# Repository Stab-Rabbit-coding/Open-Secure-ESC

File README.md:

# Open Source Trustworthy Electronic Speed Control

All builds:

MCU: **TI MSPM0G3518-Q1**, package RHB (VQFN-32, 5x5mm), orderable `M0G3518QRHBRQ1` [44] — pin map VERIFIED, standard package for all builds as of 2026-09-06 (`docs/solutions/architecture-patterns/bom-creepage-audit-can485-faraday.md` finding #1; supersedes the PM/LQFP-64 package, same die, ~4x smaller footprint). Supersedes the NXP S32K144 [31] as of 2026-08-10 (`TODO.md` §13.1; migration record in [`docs/HANDOFF-mcu-swap-s32k144-to-mspm0g3518.md`](docs/HANDOFF-mcu-swap-s32k144-to-mspm0g3518.md)), for its AES-128/256 accelerator with GCM/CMAC and hardware keystore, which lifted the AES-128 ceiling the S32K144's SHE-compliant CSEc imposed.

> **The two lines below still describe the S32K144 and its CSEc, which is no longer the MCU in any build.** They are left in place because the swap's *security* consequences are unfinished work, not a documentation lag — `docs/secure-element-architecture.md` has not yet been revisited (`TODO.md` §13.1.e), so rewriting the summary here would assert a conclusion nobody has reached. Treat every CSEc statement below as describing a superseded design until §13.1.e closes. The OPTIGA Trust M's role is unaffected: the MSPM0's AES engine is still symmetric, so the asymmetric layer is still required.

Message authentication: on-chip CSEc (Cryptographic Services Engine, SHE-compliant) security module built into the S32K144 [31] — no discrete TPM (the previously used Infineon SLB9672 [2] has been dropped from this design)
Root of trust: Infineon OPTIGA™ Trust M V3 secure element [45] over I²C (schematic `U2`) — device identity (ECDSA over a fab-provisioned key + X.509 certificate) and ephemeral session-key agreement (ECDHE). This is a secure element, **not** a TPM: it supplies the asymmetric layer CSEc structurally lacks, while CSEc keeps the per-frame AES-128 CMAC hot path. The split, and the 5 s security-monitor budget that forces it, are documented in [`docs/secure-element-architecture.md`](docs/secure-element-architecture.md)

Build Options:

* Motor speed sensor: ADC/DIO/SPI shaft sensor input (Hall / encoder / analog tach / magnetic absolute SSI-SPI, e.g. AEAT-8800-Q24 [64])
* Motor type: Brushed (Tier-1 integrated H-bridge DRV8874-Q1 [63]) / Brushless
* Holding brake: None (default) / Low-side solenoid driver, spring-applied (de-energised = engaged; TPL7407L [66]) — see `docs/decision-matrix.xlsx` "Holding Brake"
* Voltage: 2S, 4S, 6S, 8S, 12S
* Amperage: 10A, 20A, 30A, 40A, 50A, 80A, 120A
* Protocol: PWM, SBus, DBus, UART, TTL, SPI, RS-232 [3], RS-485 [4], CAN2.0 [5], CAN-FD [6], MIL-STD-1553B [7]
* Control: Open, Closed-Diff, Closed-PID
* EMI Hardening: None, Isolation, Grounding, Faraday
* Wire Egress: Opposite-end (default), Same-end opposite faces (both conductor groups leave one board end, phases on F.Cu and pack on B.Cu, shielded by the inner GND planes)
* Form Factor: Flat (default), Faceted rigid-flex (for mounting inside a curved host; strip width and sagitta derive from the host bore radius — see `docs/tools/strip_width.py`)
* Ingress & environmental protection: Splash/spray variants (target IPX4–IPX6, IEC 60529 [56]) air-cooled via an open aspirated path; Sealed/immersion variants (target IPX7–IPX8, up to NEMA 6P equivalent) shall use a metal conduction cooling path with no air exchange — these are two distinct mechanical designs, not one IP-rating dial (see `docs/design-waterproofing-and-thermal-management.md`).

## Repository layout

* `symbols/` — shared KiCad symbol library (one `.kicad_sym` per component),
  generated from citable pin specs; see `symbols/README.md`.
* `builds/<voltage>/<amperage>/<variant>/` — per-build instantiation of the
  axis options above: a descriptive `README.md` (BOM drawn from
  `docs/decision-matrix.xlsx`, with citations), a `kicad/` subfolder
  (schematic + shared-library wiring), and a `gerbers/` subfolder
  (fabrication output once a layout exists). Example:
  `builds/6s/50A/CAN_485_faraday/`.
* `docs/decision-matrix.xlsx` — per-axis BOM/workflow decision matrix that
  every build folder is generated from.
* `PROJECT_INDEX.md` — index of every active folder and file, with the
  conventions worth knowing before editing.

## License

Licensed under the CERN Open Hardware Licence Version 2 — Permissive
(CERN-OHL-P v2) [8]. See `LICENSE`.

## Governance

Contributions (human or AI) are governed by `AGENTS.md`. All citations
above are indexed in `REFERENCES.md`. Work is tracked in `TODO.md`.

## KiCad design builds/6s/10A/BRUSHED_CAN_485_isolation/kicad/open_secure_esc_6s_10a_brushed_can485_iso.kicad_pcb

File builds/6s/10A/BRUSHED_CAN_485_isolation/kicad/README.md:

# kicad/ — 6S / 10A / BRUSHED / CAN-FD+RS-485 / Isolation

Governed by `AGENTS.md`. Build spec: `../README.md`. Plan: Serenity-UAV
`docs/plans/2026-09-17-001-feat-tilt-controller-open-secure-esc-build-plan.md` (U4).

## Status

| Item | State (2026-09-17) |
| --- | --- |
| Schematic | Generated by `tools/gen_schematic.py`; **ERC 0 errors / 0 warnings** at `--severity-all` (kicad-cli 9.0.2, project context) |
| Netlist | 90 nets, 81 parts; every intended net present, no single-pin nets, PMODE → GND, IMODE strap, nFAULT pull-up, BRAKE_EN pull-down and VM-sense divider all confirmed from `kicad-cli sch export netlist` |
| PCB | Not started — no `.kicad_pcb`; see `../gerbers/README.md` for the gate list |
| Envelope check | `docs/tools/isolation_envelope.py --widest 7.0 --board-width 36.5` → minimum width 25.96 mm for the widest non-isolated part (a 7 mm inductor class) to sit between the two isolated rows; at 36.5 mm the check passes with 12.8 mm of margin, so control sits alongside comms with no creepage band in the stack |

## How the sheet is built (read before editing)

The schematic is **label-wired, not drawn**: every pin that carries a net has
a global label placed on its connection point and every unused pin has a
no-connect flag there. There are no wires. This is deliberate — it removes
the hand-wiring Y-sign trap (`docs/solutions/architecture-patterns/schematic-pin-y-sign-when-hand-wiring.md`)
and makes the netlist the proof of connectivity. The consequence is that the
sheet is a netlist you can open in KiCad, not a diagram arranged for
reading; a human-arranged view is a follow-up (`TODO.md` 18.6).

`tools/gen_schematic.py` is the single source. It reads pin geometry from the
same `symbols/*.kicad_sym` files it embeds, so a regenerated symbol cannot
drift from the sheet. `python3 tools/gen_schematic.py --check` exits 0 only
when the committed sheet equals the generator output — run it before every
commit that touches either. **Do not edit the `.kicad_sch` by hand**; if
KiCad's GUI is used to rearrange it, port the change into the generator
or the next regeneration will drop it (the 6S/50A build's divergence trap).

## Files

| File | What it is |
| --- | --- |
| `open_secure_esc_6s_10a_brushed_can485_iso.kicad_sch` | The schematic (KiCad 9 format 20250114), generated |
| `open_secure_esc_6s_10a_brushed_can485_iso.kicad_pro` | Project file: net classes Default / Power (1.5 mm) / Motor (1.5 mm) / Isolated / Sense with the net assignments below |
| `open_secure_esc_6s_10a_brushed_can485_iso.kicad_dru` | Custom rules: power/motor/sense conductor spacing, isolation-barrier no-via rule (7.5 mm, [9] Table 6) with its negative control |
| `sym-lib-table` | Symbol bindings to `symbols/`, each `descr` carrying the REFERENCES tag and verification note |
| `fp-lib-table` | `Open_Secure_ESC.pretty` (this repo's TI PWP0016J / DDA0008B / OPTIGA USON-10 footprints) |
| `tools/gen_schematic.py` | Generator (kiutils-free) |

## Net classes

| Class | Nets | Why |
| --- | --- | --- |
| Power | VBAT, GND, VMOT, 3V3, U6_SW, U8_SW | 3 A branch, 2.9 A motor stall; width sized in the layout follow-up (IPC-2152 [46] unread) |
| Motor | MOT_OUT1, MOT_OUT2, SOL_N | Bridge outputs and the solenoid sink |
| Isolated | CAN_H/L, CAN_VISOIN/OUT, CAN_ISO_GND, CAN_GNDISO, RS485_A/B, RS485_VISOIN/OUT, RS485_ISO_GND, RS485_GNDISO | Isolated side of both transceivers; the `.kicad_dru` via rule keys on this class |
| Sense | ADC_IPROPI, ADC_VM, ADC_VBUS, BRAKE_SENSE, U5_VREF, U5_IPROPI | Analog, 0.3 mm spacing |

## Libraries (sym-lib-table)

| Nickname | Symbol | Pin-map status |
| --- | --- | --- |
| `MSPM0G3518_Q1_RHB_TILT` | U1 MCU, tilt-build role names, all 32 pins | VERIFIED — [44] Fig. 6-6 / Table 6-2 (`symbols/specs/MSPM0G3518_Q1_RHB_TILT.json`) |
| `OPTIGA_TRUST_M` | U2 | VERIFIED — [45] p.17 Table 6 |
| `ADM3055E_ADM3057E` | U3 (ADM3057E) | VERIFIED — [10]; part Candidate |
| `ADM2582E_ADM2587E` | U4 (ADM2587E) | VERIFIED — [9]; part Candidate |
| `DRV8874_Q1` | U5 | VERIFIED — [63] §5, cross-checked [62] |
| `TPS54560B` | U6, U8 | VERIFIED — [65] §5 |
| `TPL7407L` | U7 | VERIFIED — [66] §5 |
| `BLM15HD182SN1D` | FB1–FB4 | VERIFIED — [53] |
| `AEAT_8800_Q24` | (not placed; off-board sensor daughter) | VERIFIED — [64] |
| `Open_Secure_ESC_Generic` | R, C, Conn_01x02/04, PWR_FLAG | Generic |
| `Device`, `Connector_Generic` (KiCad stock) | L1/L2, D1/D2, J7 | Generic; parts UNVERIFIED — see `../README.md` |

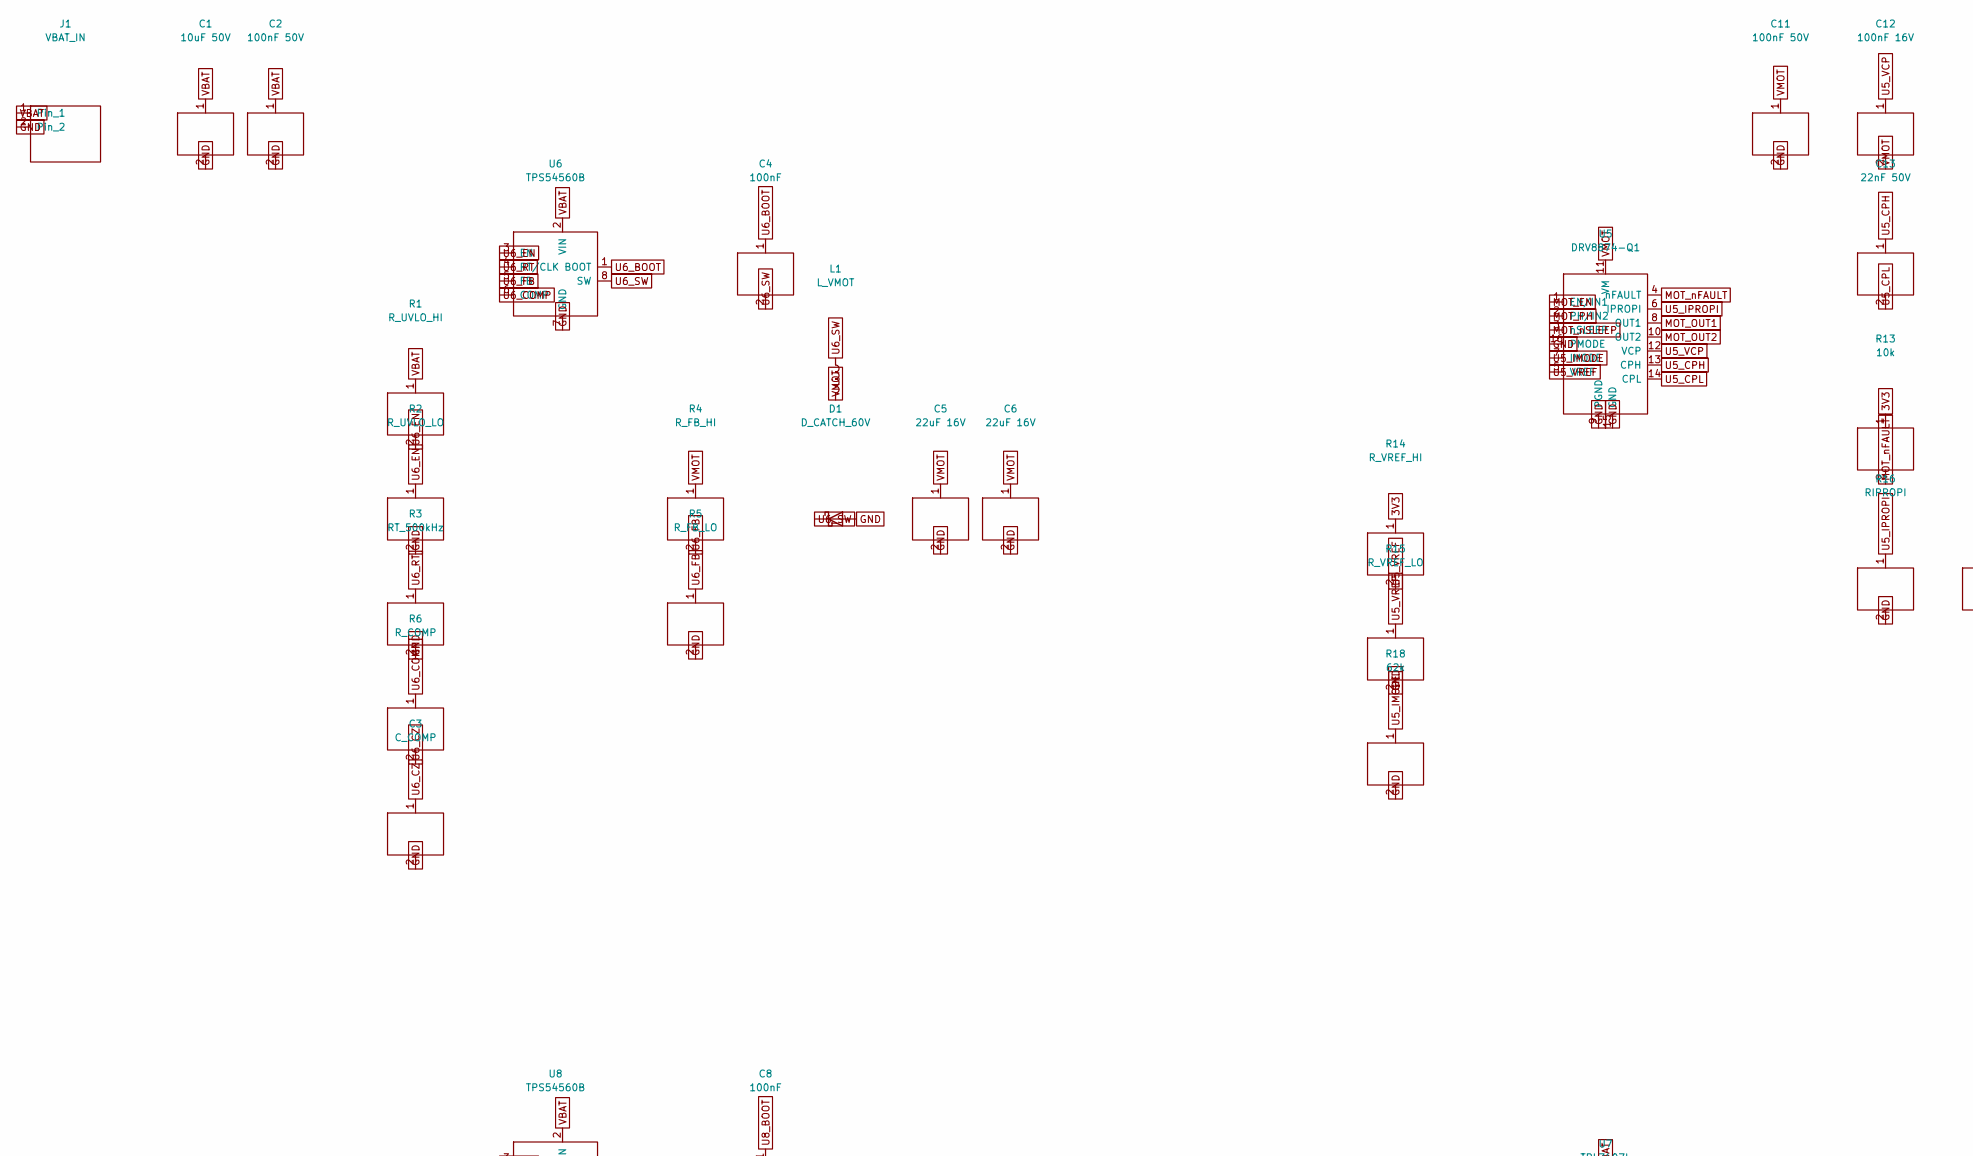
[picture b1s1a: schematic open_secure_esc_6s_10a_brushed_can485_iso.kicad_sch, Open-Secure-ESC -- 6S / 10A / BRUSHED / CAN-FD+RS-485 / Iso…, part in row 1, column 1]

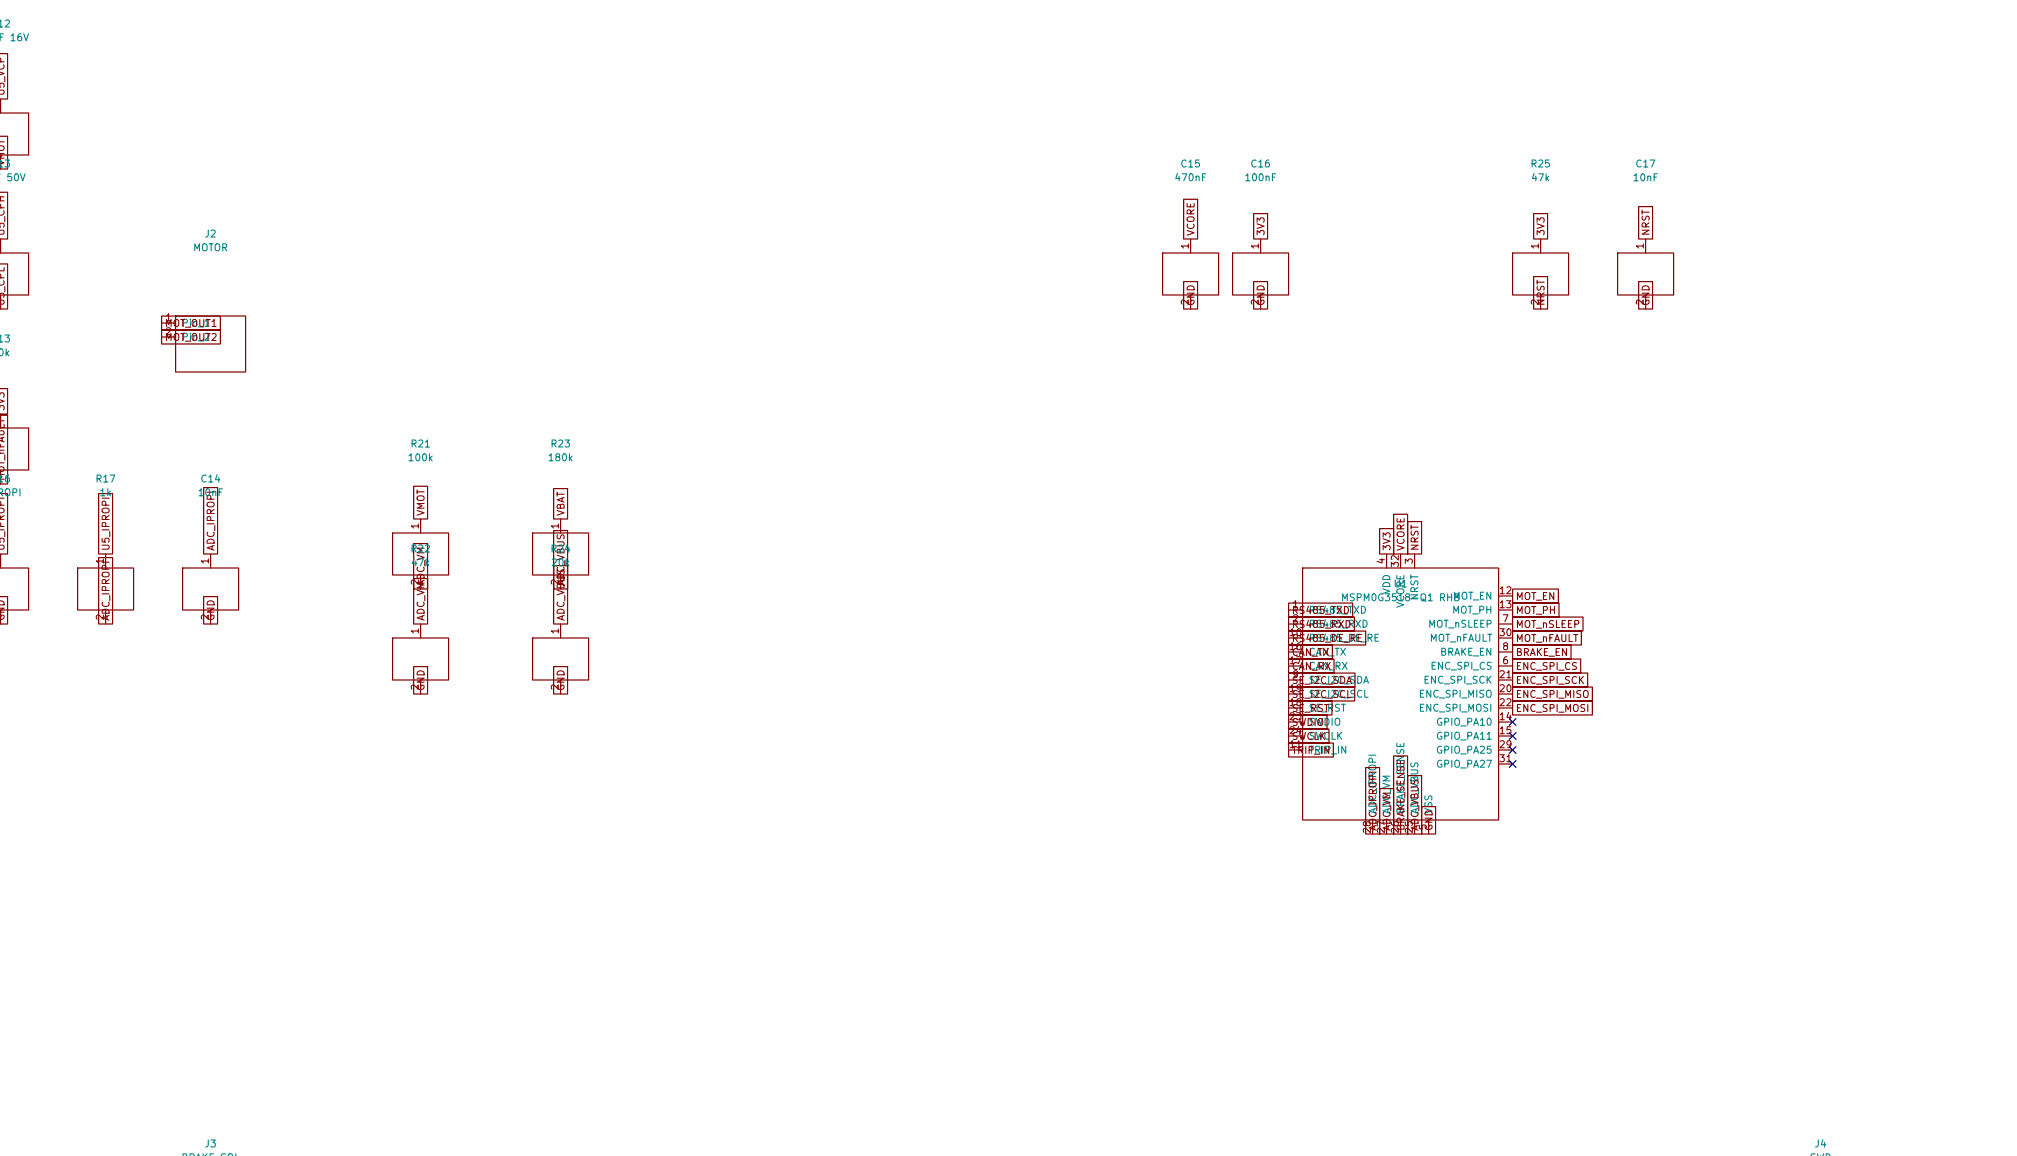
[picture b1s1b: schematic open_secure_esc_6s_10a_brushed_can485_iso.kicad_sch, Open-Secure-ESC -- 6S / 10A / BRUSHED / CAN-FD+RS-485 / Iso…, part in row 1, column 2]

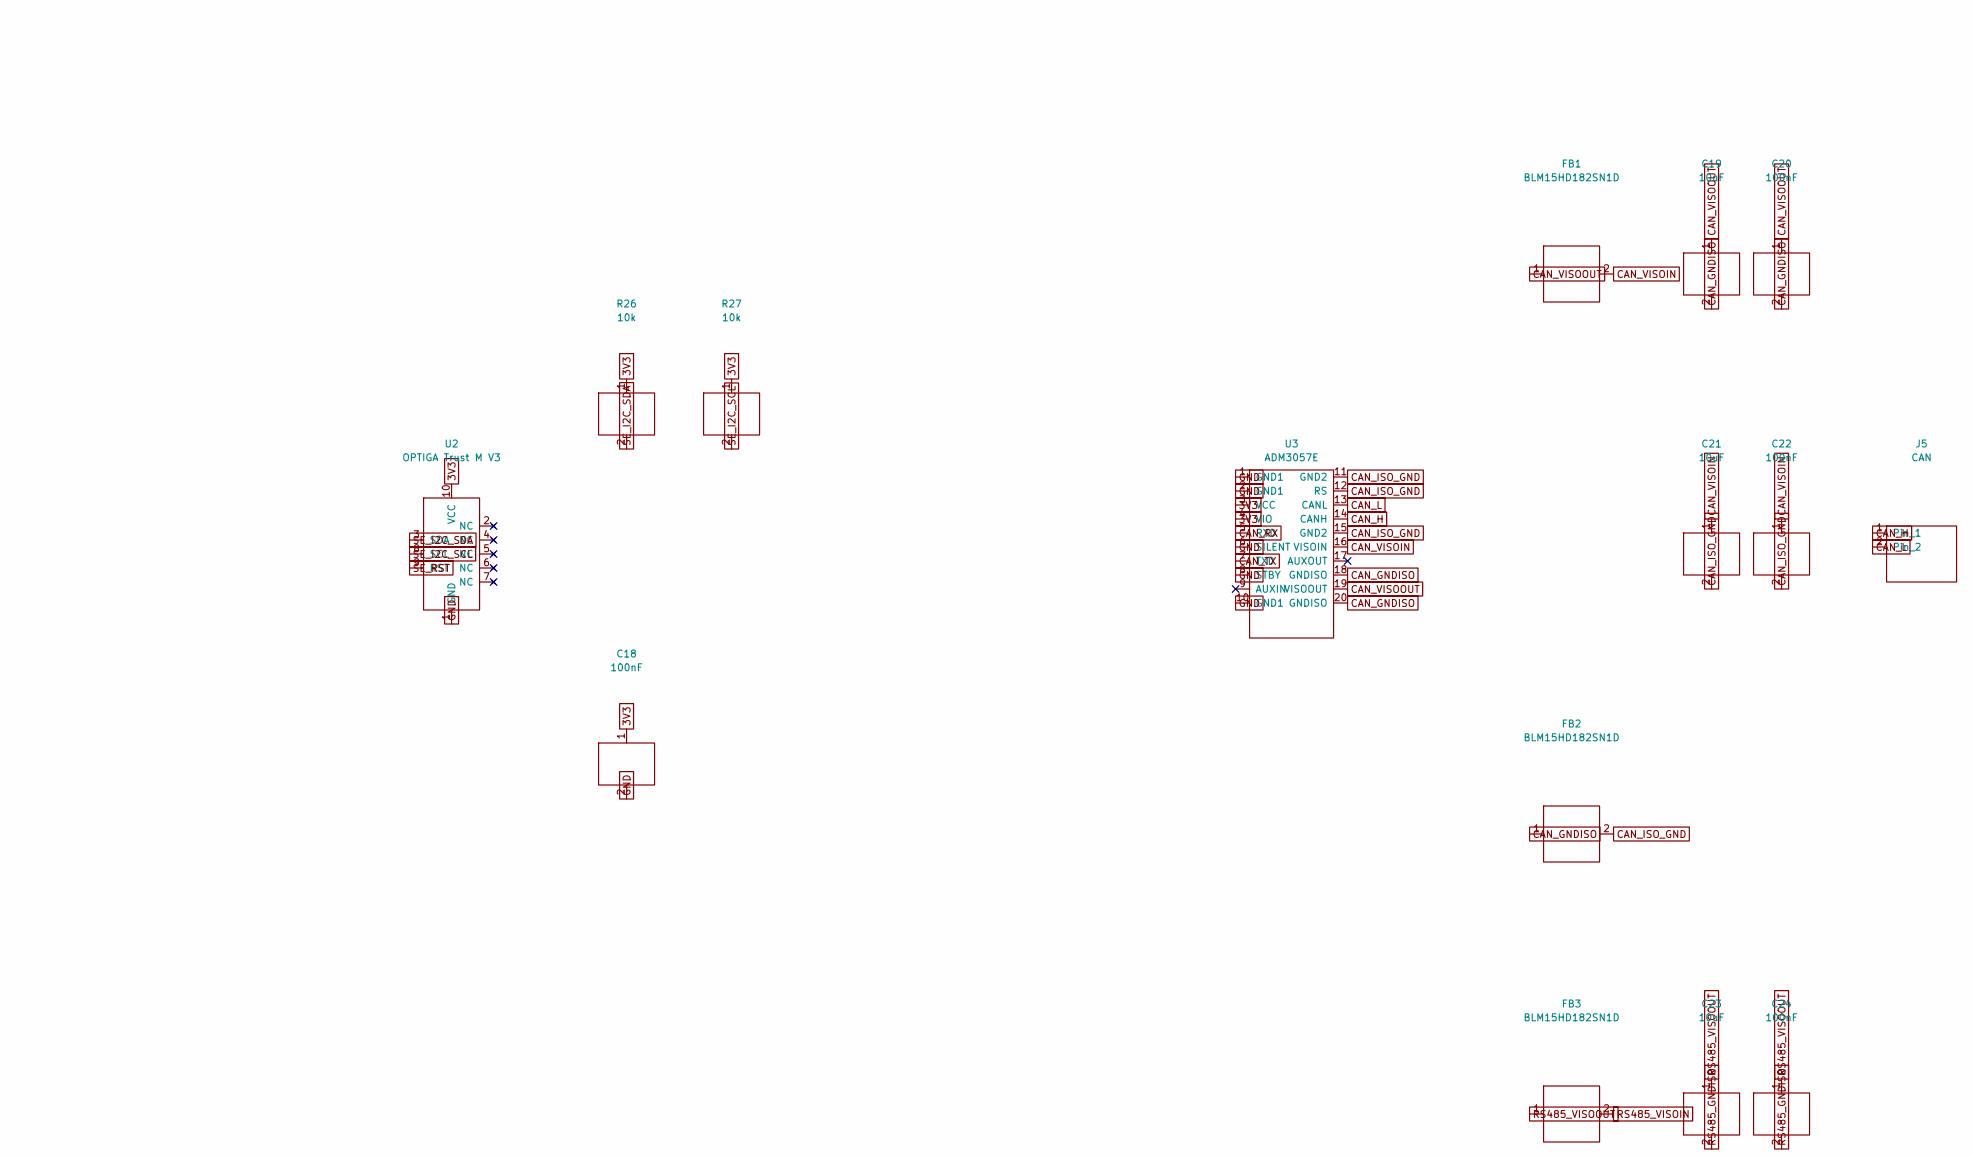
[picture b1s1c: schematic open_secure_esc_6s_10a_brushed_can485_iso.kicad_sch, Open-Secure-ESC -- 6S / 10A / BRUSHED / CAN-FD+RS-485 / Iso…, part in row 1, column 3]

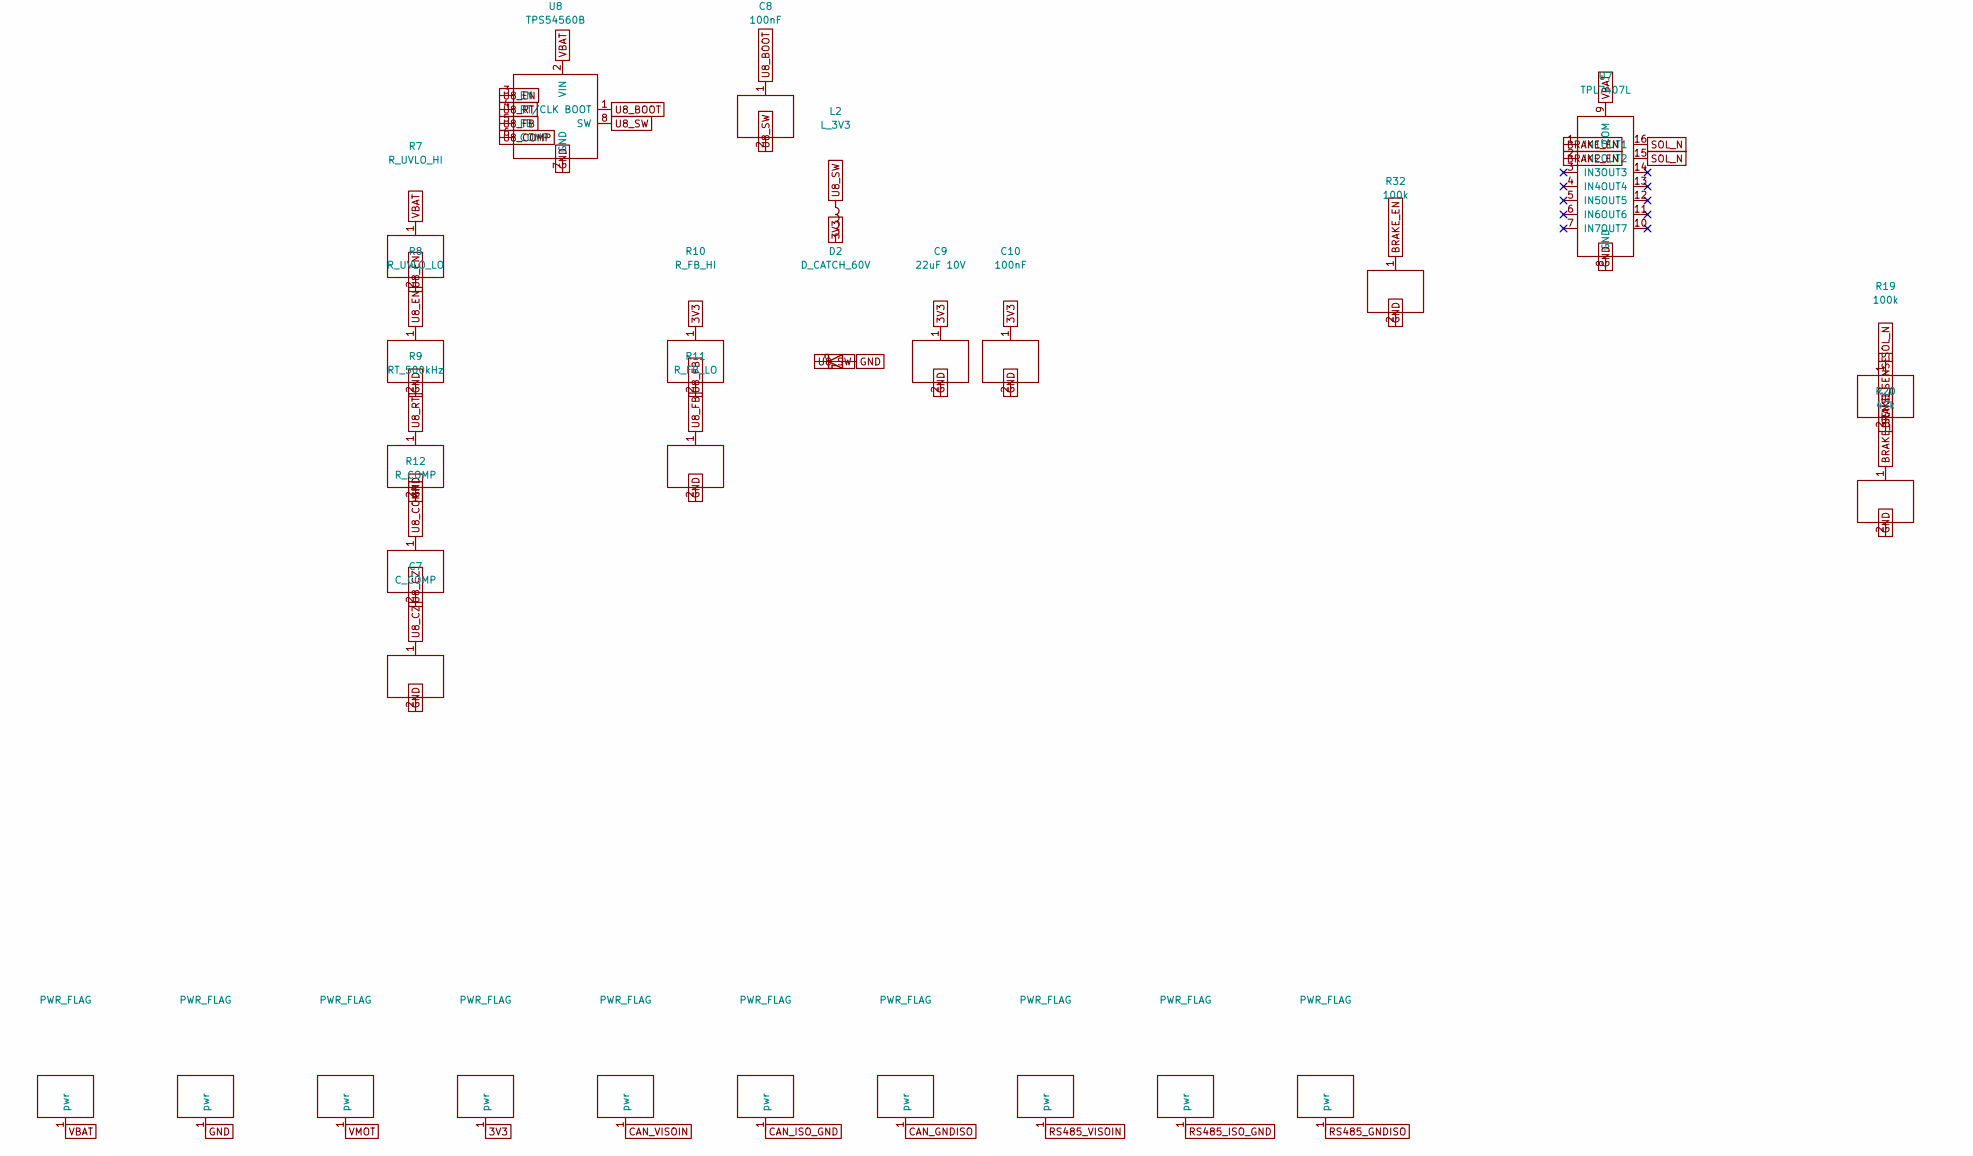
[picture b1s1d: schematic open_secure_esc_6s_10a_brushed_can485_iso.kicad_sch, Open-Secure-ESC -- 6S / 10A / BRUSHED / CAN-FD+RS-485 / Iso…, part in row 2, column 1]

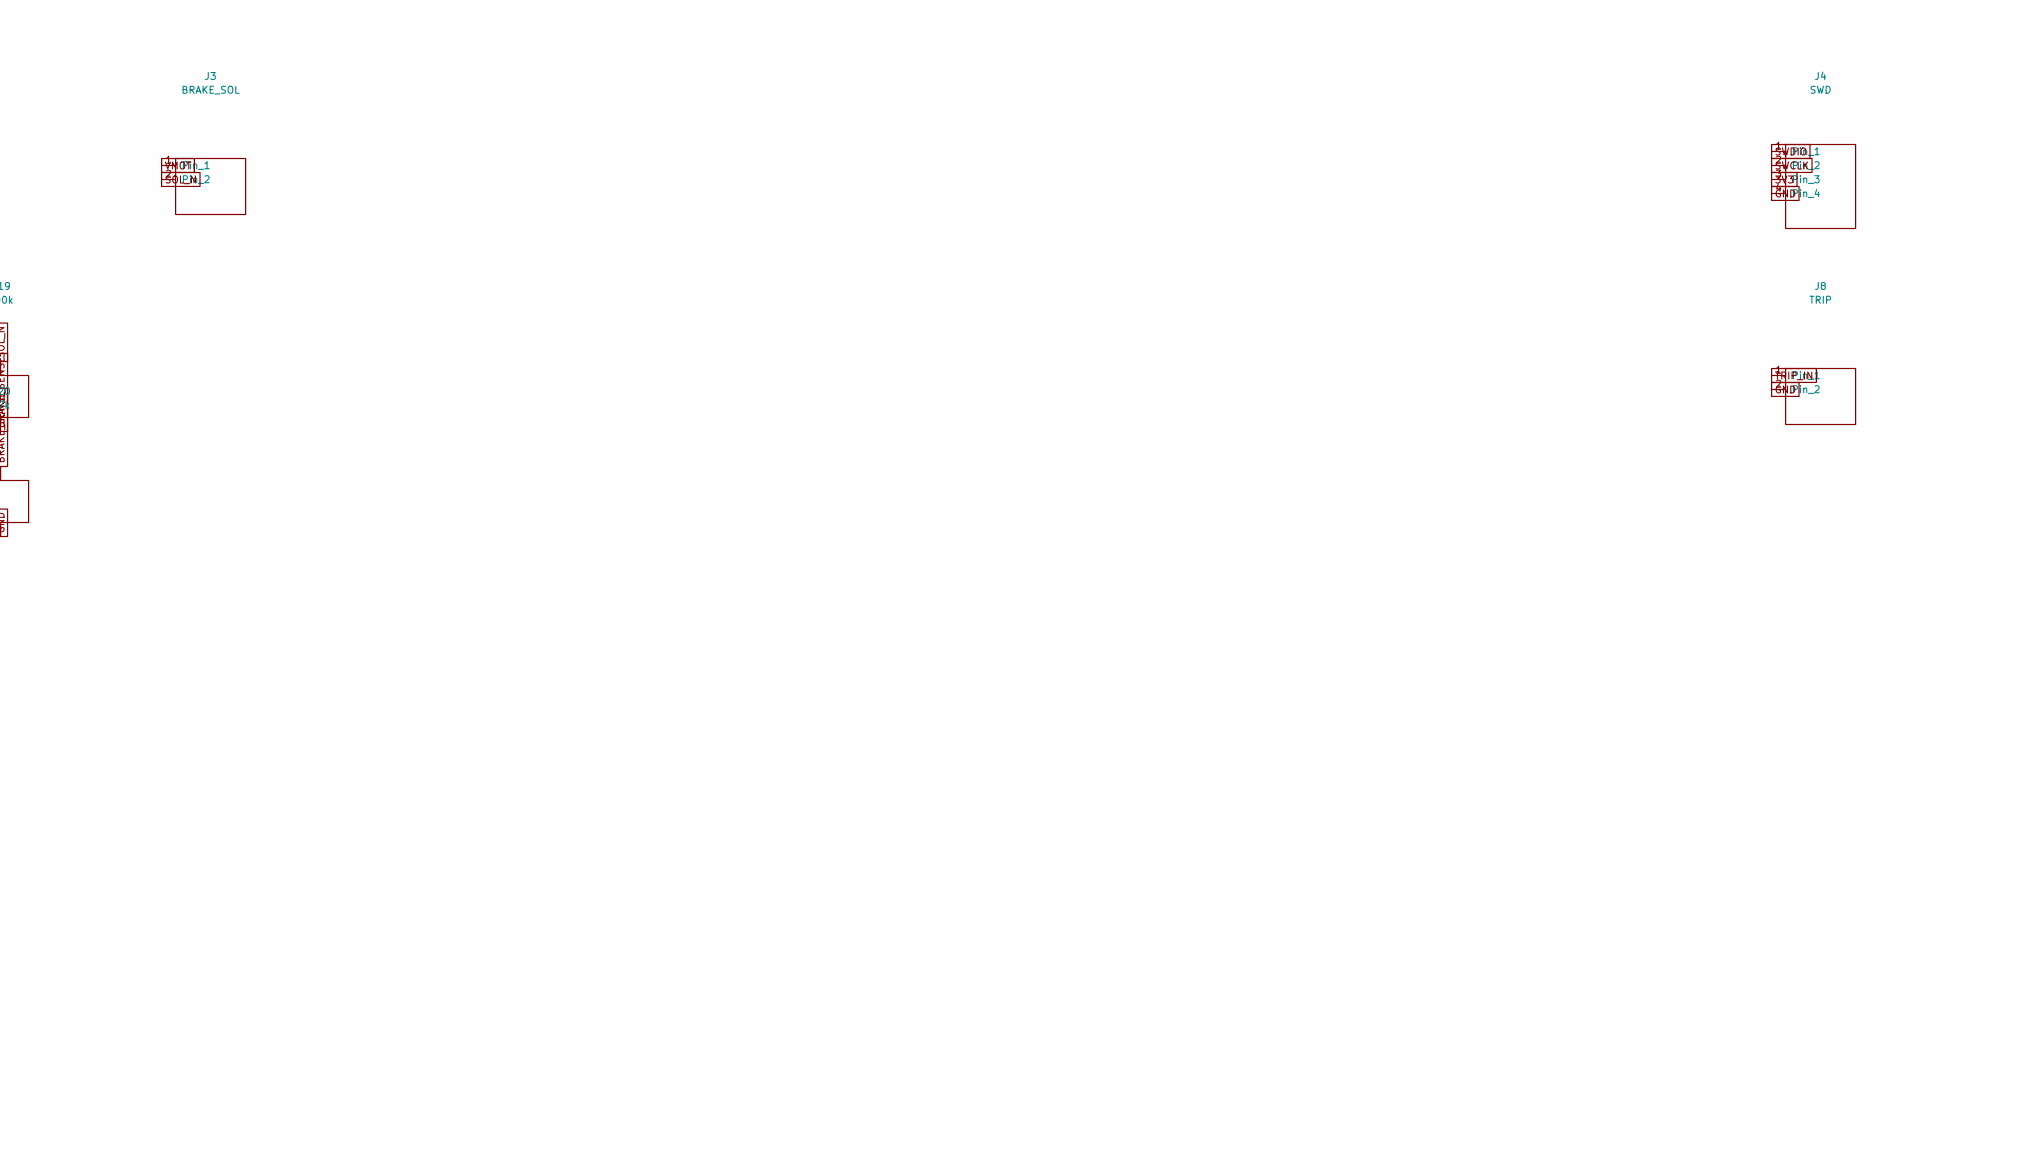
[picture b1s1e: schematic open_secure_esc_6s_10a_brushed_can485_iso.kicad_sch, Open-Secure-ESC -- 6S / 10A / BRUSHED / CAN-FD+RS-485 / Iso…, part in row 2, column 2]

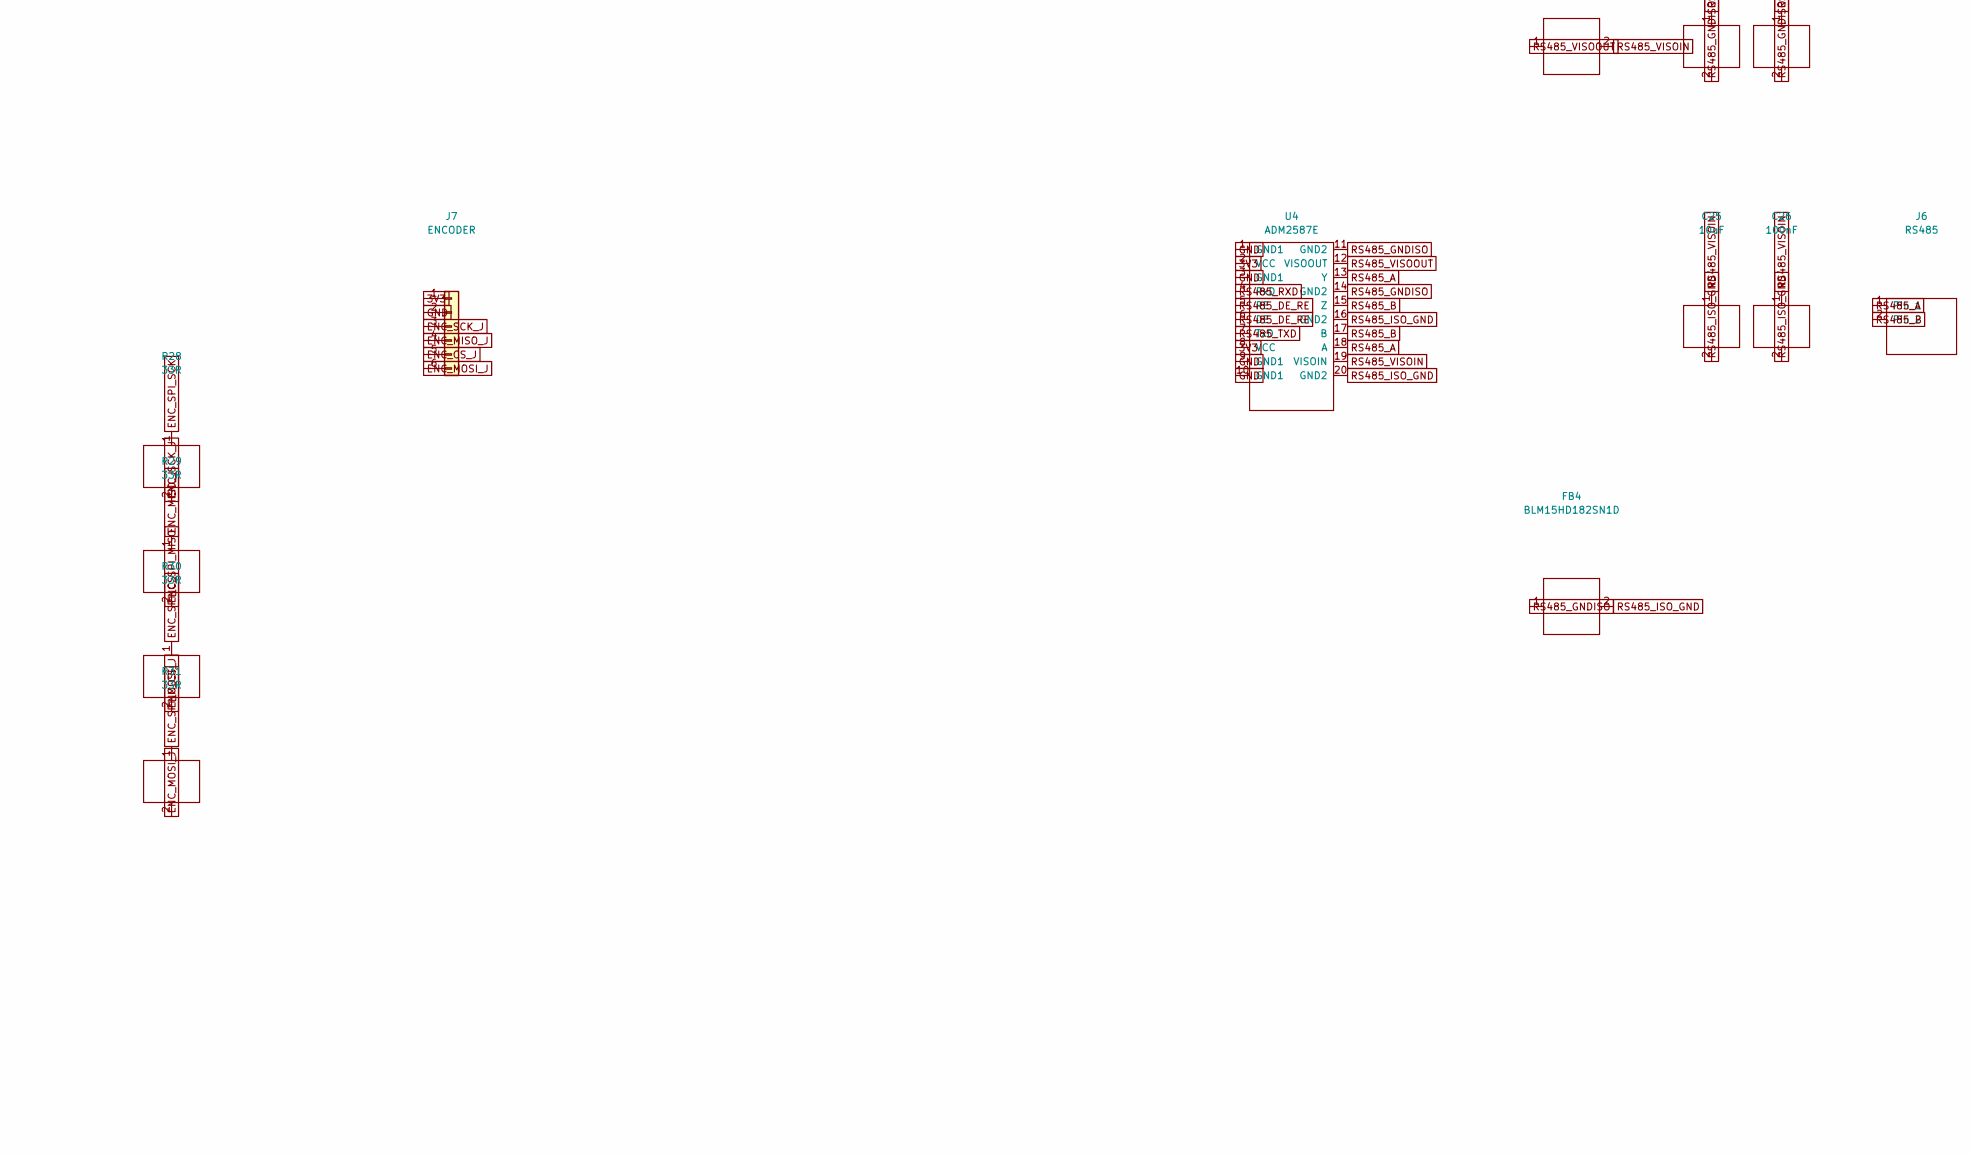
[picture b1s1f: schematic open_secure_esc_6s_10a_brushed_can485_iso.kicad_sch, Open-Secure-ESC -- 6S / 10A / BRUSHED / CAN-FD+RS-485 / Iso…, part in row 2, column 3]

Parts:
C1: 10uF 50V; C_1210_3225Metric
C2, C11: 100nF 50V; C_0603_1608Metric
C3, C7: C_COMP; C_0603_1608Metric
C4, C8, C10, C16, C18, C20, C22, C24, C26: 100nF; C_0603_1608Metric
C5, C6: 22uF 16V; C_1210_3225Metric
C9: 22uF 10V; C_1210_3225Metric
C12: 100nF 16V; C_0603_1608Metric
C13: 22nF 50V; C_0603_1608Metric
C14, C17: 10nF; C_0603_1608Metric
C15: 470nF; C_0603_1608Metric
C19, C21, C23, C25: 10uF; C_0603_1608Metric
D1, D2: D_CATCH_60V; D_SMA
FB1, FB2, FB3, FB4: BLM15HD182SN1D; L_0402_1005Metric
J1: VBAT_IN; JST_XH_B2B-XH-A_1x02_P2.50mm_Vertical
J2: MOTOR; JST_XH_B2B-XH-A_1x02_P2.50mm_Vertical
J3: BRAKE_SOL; JST_XH_B2B-XH-A_1x02_P2.50mm_Vertical
J4: SWD; PinHeader_1x04_P1.27mm_Vertical
J5: CAN; JST_XH_B2B-XH-A_1x02_P2.50mm_Vertical
J6: RS485; JST_XH_B2B-XH-A_1x02_P2.50mm_Vertical
J7: ENCODER; JST_GH_BM06B-GHS-TBT_1x06-1MP_P1.25mm_Vertical
J8: TRIP; PinHeader_1x02_P1.27mm_Vertical
L1: L_VMOT; L_Wuerth_HCI-5040
L2: L_3V3; L_Wuerth_HCI-5040
R1, R7: R_UVLO_HI; R_0603_1608Metric
R2, R8: R_UVLO_LO; R_0603_1608Metric
R3, R9: RT_500kHz; R_0603_1608Metric
R4, R10: R_FB_HI; R_0603_1608Metric
R5, R11: R_FB_LO; R_0603_1608Metric
R6, R12: R_COMP; R_0603_1608Metric
R13, R26, R27: 10k; R_0603_1608Metric
R14: R_VREF_HI; R_0603_1608Metric
R15: R_VREF_LO; R_0603_1608Metric
R16: RIPROPI; R_0603_1608Metric
R17: 1k; R_0603_1608Metric
R18: 62k; R_0603_1608Metric
R19, R21, R32: 100k; R_0603_1608Metric
R20, R22, R25: 47k; R_0603_1608Metric
R23: 180k; R_0603_1608Metric
R24: 20k; R_0603_1608Metric
R28, R29, R30, R31: 33R; R_0603_1608Metric
U1: MSPM0G3518-Q1 RHB; Texas_RHB0032E_VQFN-32-1EP_5x5mm_P0.5mm_EP3.45x3.45mm
U2: OPTIGA Trust M V3; Infineon_PG-USON-10-2-4_3x3mm_P0.5mm_EP1.7x2.5mm
U3: ADM3057E; SOIC-20W_7.5x12.8mm_P1.27mm
U4: ADM2587E; SOIC-20W_7.5x12.8mm_P1.27mm
U5: DRV8874-Q1; TI_PWP0016J_HTSSOP-16_4.4x5mm_P0.65mm_EP2.46x3.55mm
U6, U8: TPS54560B; TI_DDA0008B_HSOIC-8_3.9x4.9mm_P1.27mm_EP2.71x3.4mm
U7: TPL7407L; TSSOP-16_4.4x5mm_P0.65mm

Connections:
3V3: C9.1, C10.1, C16.1, C18.1, J4.3, J7.1, L2.2, R10.1, R13.1, R14.1, R25.1, R26.1, R27.1, U1.4 (VDD), U2.10 (VCC), U3.3 (VCC), U3.4 (VIO), U4.2 (VCC), U4.8 (VCC)
ADC_IPROPI: C14.1, R17.2, U1.28 (ADC_IPROPI)
ADC_VBUS: R23.2, R24.1, U1.25 (ADC_VBUS)
ADC_VM: R21.2, R22.1, U1.27 (ADC_VM)
BRAKE_EN: R32.1, U1.8 (BRAKE_EN), U7.1 (IN1), U7.2 (IN2)
BRAKE_SENSE: R19.2, R20.1, U1.26 (BRAKE_SENSE)
CAN_GNDISO: C19.2, C20.2, FB2.1, U3.18 (GNDISO), U3.20 (GNDISO)
CAN_H: J5.1, U3.14 (CANH)
CAN_ISO_GND: C21.2, C22.2, FB2.2, U3.11 (GND2), U3.12 (RS), U3.15 (GND2)
CAN_L: J5.2, U3.13 (CANL)
CAN_RX: U1.17 (CAN_RX), U3.5 (RXD)
CAN_TX: U1.16 (CAN_TX), U3.7 (TXD)
CAN_VISOIN: C21.1, C22.1, FB1.2, U3.16 (VISOIN)
CAN_VISOOUT: C19.1, C20.1, FB1.1, U3.19 (VISOOUT)
ENC_CS_J: J7.5, R30.2
ENC_MISO_J: J7.4, R29.1
ENC_MOSI_J: J7.6, R31.2
ENC_SCK_J: J7.3, R28.2
ENC_SPI_CS: R30.1, U1.6 (ENC_SPI_CS)
ENC_SPI_MISO: R29.2, U1.20 (ENC_SPI_MISO)
ENC_SPI_MOSI: R31.1, U1.22 (ENC_SPI_MOSI)
ENC_SPI_SCK: R28.1, U1.21 (ENC_SPI_SCK)
GND: C1.2, C2.2, C3.2, C5.2, C6.2, C7.2, C9.2, C10.2, C11.2, C14.2, C15.2, C16.2, C17.2, C18.2, D1.2 (A), D2.2 (A), J1.2, J4.4, J7.2, J8.2, R2.2, R3.2, R5.2, R8.2, R9.2, R11.2, R15.2, R16.2, R18.2, R20.2, R22.2, R24.2, R32.2, U1.5 (VSS), U2.1 (GND), U3.1 (GND1), U3.2 (GND1), U3.6 (SILENT), U3.8 (STBY), U3.10 (GND1), U4.1 (GND1), U4.3 (GND1), U4.9 (GND1), U4.10 (GND1), U5.9 (PGND), U5.15 (GND), U5.16 (PMODE), U6.7 (GND), U7.8 (GND), U8.7 (GND)
MOT_EN: U1.12 (MOT_EN), U5.1 (EN/IN1)
MOT_OUT1: J2.1, U5.8 (OUT1)
MOT_OUT2: J2.2, U5.10 (OUT2)
MOT_PH: U1.13 (MOT_PH), U5.2 (PH/IN2)
MOT_nFAULT: R13.2, U1.30 (MOT_nFAULT), U5.4 (nFAULT)
MOT_nSLEEP: U1.7 (MOT_nSLEEP), U5.3 (nSLEEP)
NRST: C17.1, R25.2, U1.3 (NRST)
RS485_A: J6.1, U4.13 (Y), U4.18 (A)
RS485_B: J6.2, U4.15 (Z), U4.17 (B)
RS485_DE_RE: U1.10 (RS485_DE_RE), U4.5 (RE), U4.6 (DE)
RS485_GNDISO: C23.2, C24.2, FB4.1, U4.11 (GND2), U4.14 (GND2)
RS485_ISO_GND: C25.2, C26.2, FB4.2, U4.16 (GND2), U4.20 (GND2)
RS485_RXD: U1.2 (RS485_RXD), U4.4 (RxD)
RS485_TXD: U1.1 (RS485_TXD), U4.7 (TxD)
RS485_VISOIN: C25.1, C26.1, FB3.2, U4.19 (VISOIN)
RS485_VISOOUT: C23.1, C24.1, FB3.1, U4.12 (VISOOUT)
SE_I2C_SCL: R27.2, U1.19 (SE_I2C_SCL), U2.8 (SCL)
SE_I2C_SDA: R26.2, U1.9 (SE_I2C_SDA), U2.3 (SDA)
SE_RST: U1.18 (SE_RST), U2.9 (RST)
SOL_N: J3.2, R19.1, U7.15 (OUT2), U7.16 (OUT1)
SWCLK: J4.2, U1.24 (SWCLK)
SWDIO: J4.1, U1.23 (SWDIO)
TRIP_IN: J8.1, U1.11 (TRIP_IN)
U5_CPH: C13.1, U5.13 (CPH)
U5_CPL: C13.2, U5.14 (CPL)
U5_IMODE: R18.1, U5.7 (IMODE)
U5_IPROPI: R16.1, R17.1, U5.6 (IPROPI)
U5_VCP: C12.1, U5.12 (VCP)
U5_VREF: R14.2, R15.1, U5.5 (VREF)
U6_BOOT: C4.1, U6.1 (BOOT)
U6_COMP: R6.1, U6.6 (COMP)
U6_CZ: C3.1, R6.2
U6_EN: R1.2, R2.1, U6.3 (EN)
U6_FB: R4.2, R5.1, U6.5 (FB)
U6_RT: R3.1, U6.4 (RT/CLK)
U6_SW: C4.2, D1.1 (K), L1.1, U6.8 (SW)
U8_BOOT: C8.1, U8.1 (BOOT)
U8_COMP: R12.1, U8.6 (COMP)
U8_CZ: C7.1, R12.2
U8_EN: R7.2, R8.1, U8.3 (EN)
U8_FB: R10.2, R11.1, U8.5 (FB)
U8_RT: R9.1, U8.4 (RT/CLK)
U8_SW: C8.2, D2.1 (K), L2.1, U8.8 (SW)
VBAT: C1.1, C2.1, J1.1, R1.1, R7.1, R23.1, U6.2 (VIN), U7.9 (COM), U8.2 (VIN)
VCORE: C15.1, U1.32 (VCORE)
VMOT: C5.1, C6.1, C11.1, C12.2, J3.1, L1.2, R4.1, R21.1, U5.11 (VM)

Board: 2 copper layers, 82 parts (0 on the bottom side), 69 nets, no tracks yet.

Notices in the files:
builds/6s/50A/CAN_485_faraday_sameend/kicad/open_secure_esc_6s_50a_can485_faraday_sameend.kicad_pcb:
CERN-OHL-P 2.0  2026
parts and their libraries:
Citation: [4], [9]
Citation: [6], [10]
Citation: [9], [10], [53]
Citation: [62], [63]
Citation: [44]
Citation: [45]
Citation: [66]
Citation: [65]
